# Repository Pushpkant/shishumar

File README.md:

Wildlife Institute of India

**Analog Timer Design**

Complete Product Design including requirement and Design.

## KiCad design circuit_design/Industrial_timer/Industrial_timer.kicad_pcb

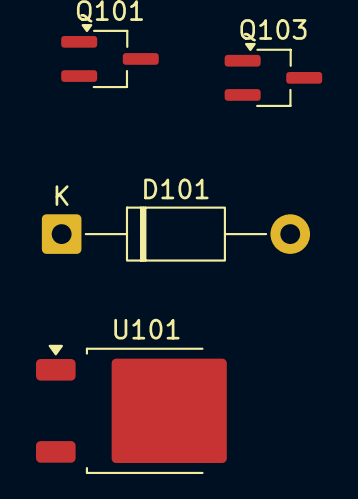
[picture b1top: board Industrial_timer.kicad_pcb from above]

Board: 2 copper layers, 4 parts (0 on the bottom side), 3 nets, no tracks yet.

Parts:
D101: 1N4007; D_DO-41_SOD81_P12.70mm_Horizontal
Q101: MMBT3904; TSOT-23_HandSoldering
Q103: DMP4065SQ; TSOT-23_HandSoldering
U101: SL78M05; TO-252-2

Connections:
GND: Q101.2 (E), U101.2 (GND)
unnamed: D101.1 (K), U101.1 (VIN)
vpow: D101.2 (A), Q103.2 (S)

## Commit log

2026-01-18 Adding Readme
2026-01-18 Adding ignore file list.
2026-01-18 Adding documents.
2026-01-18 Adding Timer circuit. Power Supply with reverse polarity protection and overvoltage protection implemented.
2026-01-18 Adding the report.
2026-01-18 Adding the plots
2026-01-18 Adding a generic RC circuit. To be removed later.
2026-01-18 Updated the users duty.
2026-02-22 Completed Power Supply block design and updated the report.
2026-02-22 Saving updated circuits.
